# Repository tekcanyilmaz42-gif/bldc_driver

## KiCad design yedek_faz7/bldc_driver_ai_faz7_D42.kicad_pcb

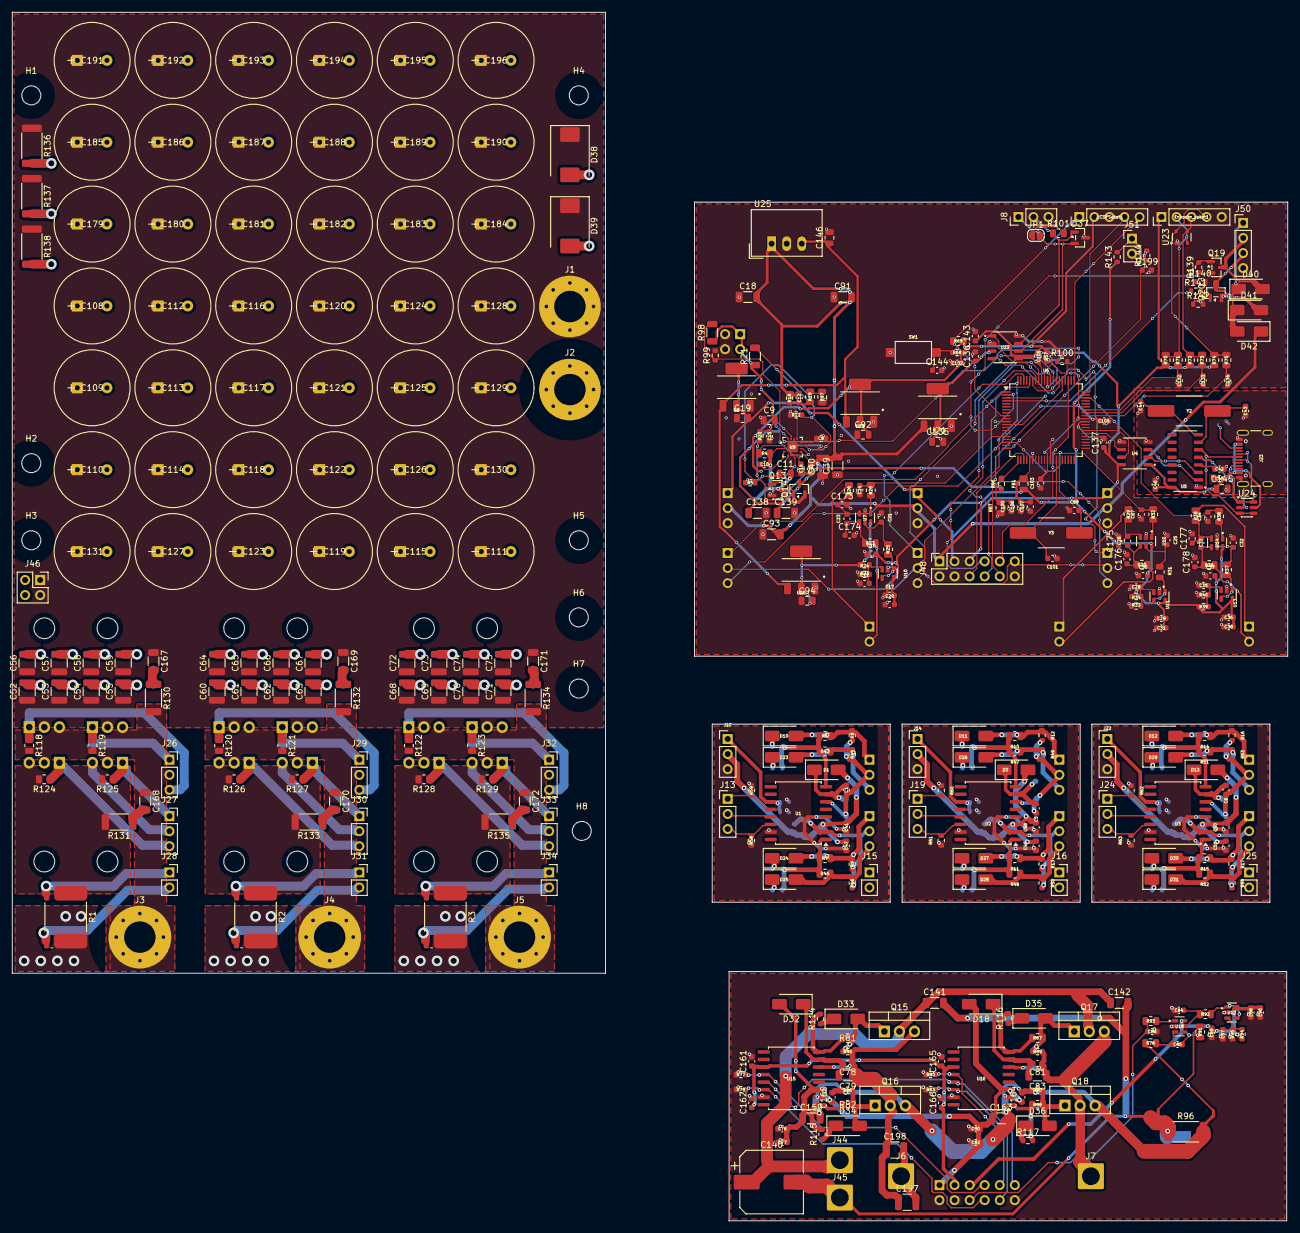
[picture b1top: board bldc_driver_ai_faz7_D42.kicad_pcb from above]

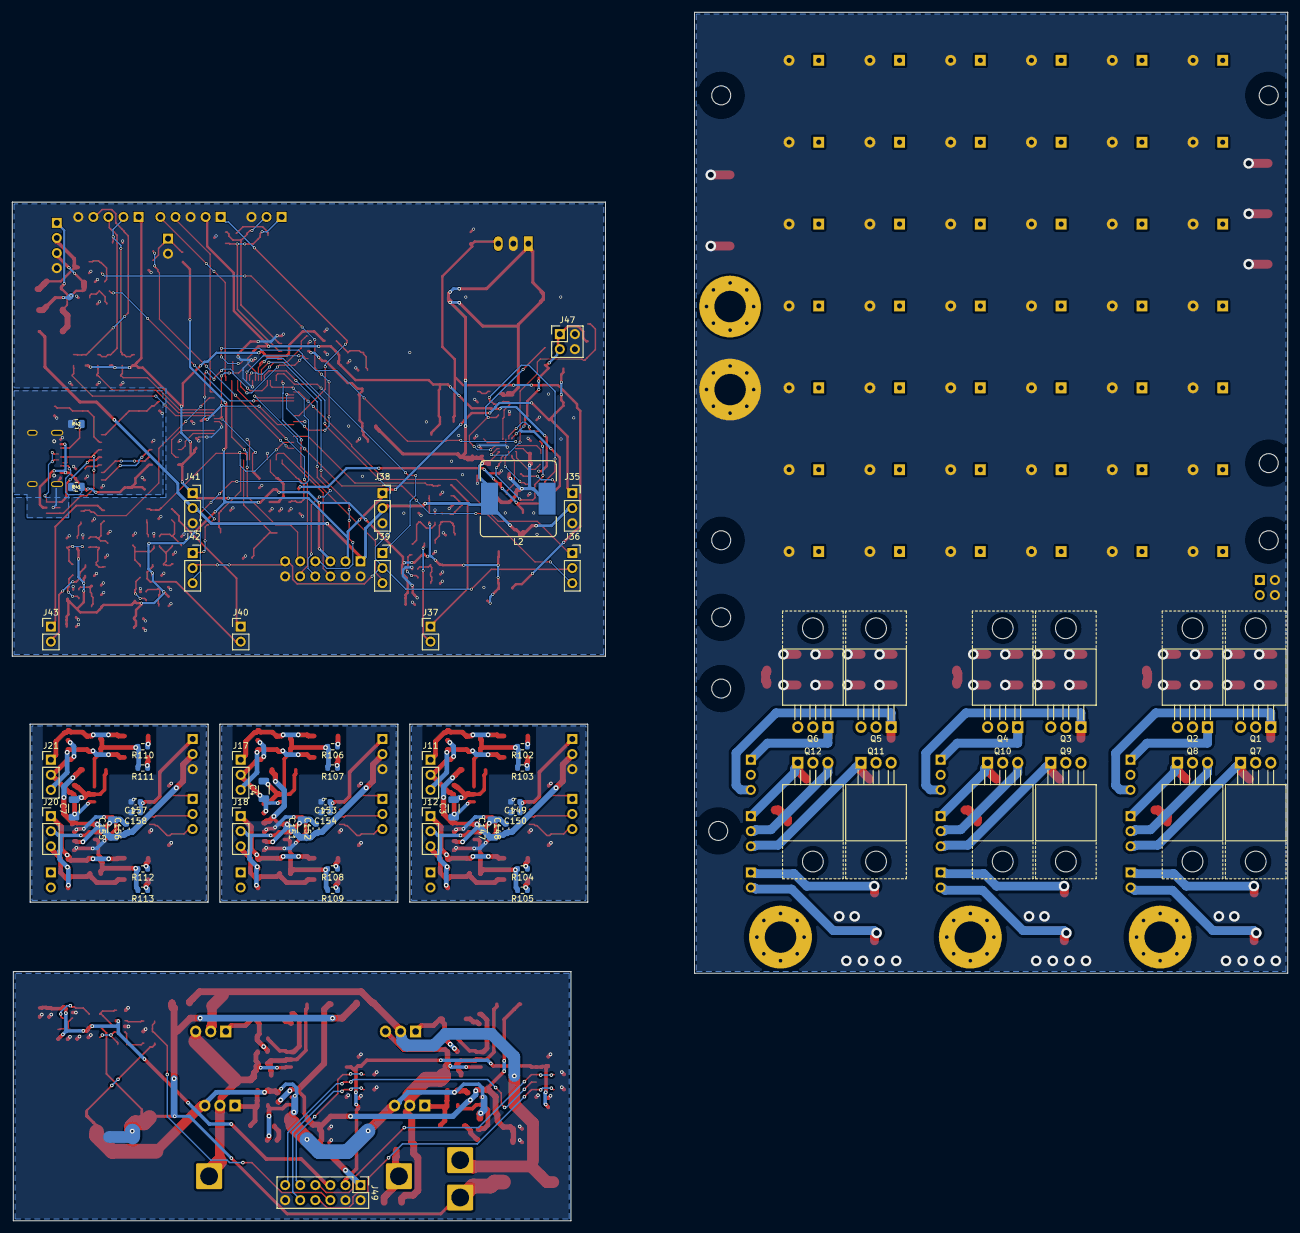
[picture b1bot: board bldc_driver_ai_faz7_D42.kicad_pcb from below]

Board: 2 copper layers, 215.0 x 203.7 mm, 473 parts (60 on the bottom side), 174 nets.

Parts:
C1, C5, C6, C10, C16, C17, C22, C28, C29, C30, C35, C36, C37, C42, C45, C46, C78, C81, C87, C88, C89, C100, C102, C103, C104, C105, C106, C136, C137, C143, C144, C148, C149, C152, C153, C156, C157, C160, C161, C164, C165, C199: 100nF; C_0603_1608Metric
C3, C4, C7, C79, C83: 2.2uF/25V; C_1206_3216Metric
C8: 10nF; C_0603_1608Metric
C9, C11: 100nF/100V; C_0805_2012Metric
C12: 4.7nF; C_0603_1608Metric
C13, C20, C31, C38, C41, C47, C48, C49, C50, C51, C76, C77, C80, C82, C90, C107, C150, C154, C158, C162, C166: 1uF; C_0603_1608Metric
C14, C15: 10uF; C_0603_1608Metric
C18, C39, C40, C91, C93: 10uF/25V; C_1206_3216Metric
C19, C92, C94, C146: 22uF/10V; C_0805_2012Metric
C21, C25, C32, C84: 1nF C0G; C_0603_1608Metric
C23, C26, C33: 220nF; C_0603_1608Metric
C24, C27, C34, C85, C86, C132, C133, C134, C173, C174, C175, C176, C177, C178: 1nF; C_0603_1608Metric
C43, C44, C99, C101: 27pF; C_0603_1608Metric
C52, C53, C54, C55, C56, C57, C58, C59, C60, C61, C62, C63, C64, C65, C66, C67, C68, C69, C70, C71, C72, C73, C74, C75, C197, C198: 4.7uF/100V; C_1210_3225Metric
C108, C109, C110, C111, C112, C113, C114, C115, C116, C117, C118, C119, C120, C121, C122, C123, C124, C125, C126, C127, C128, C129, C130, C131, C179, C180, C181, C182, C183, C184, C185, C186, C187, C188, C189, C190, C191, C192, C193, C194, C195, C196: 470uF/63V; KLH-063V471MH200-TA5.0
C135: 10uF/16V; C_0805_2012Metric
C138, C139, C141, C142: 2.2uF/100V; C_1206_3216Metric
C140: 220uF/63V; CP_Elec_10x10.5
C145: 4.7uF/10V; C_0805_2012Metric
C147, C151, C155, C159, C163: 22uF/25V; C_1206_3216Metric
C167, C168, C169, C170, C171, C172: 4.7nF/100V C0G; C_1206_3216Metric
D1, D2, D13, D18, D32: US1D; D_SMA
D10, D11, D12, D23, D24, D25, D26, D27, D28, D29, D30, D31, D33, D34, D35, D36, D40, D41: SS18; D_SMA
D37: NUP2105L; SOT-23
D38, D39: 5.0SMDJ58CA; D_SMC
D42: SS34; D_SMA
Enkoder_soket1: Conn_01x05_Socket; PinHeader_1x05_P2.54mm_Vertical
FB1: FerriteBead; C_0805_2012Metric
H1, H2, H3, H4, H5, H6, H7, H8: M3_Sogutucu; MountingHole_3.2mm_M3
J1: M5_Lug_VBAT; MountingHole_5.3mm_M5_Pad_Via
J2: M5_Lug_GND; MountingHole_5.3mm_M5_Pad_Via
J3: M5_Lug_U; MountingHole_5.3mm_M5_Pad_Via
J4: M5_Lug_V; MountingHole_5.3mm_M5_Pad_Via
J5: M5_Lug_W; MountingHole_5.3mm_M5_Pad_Via
J6, J7: Conn_01x01_Pin; SolderWire-2.5sqmm_1x01_D2.4mm_OD4.4mm
J8: CAN-bus; PinHeader_1x03_P2.54mm_Vertical
J10: Pwr_U; PinHeader_1x03_P2.54mm_Vertical
J11: Gate_H_U; PinHeader_1x03_P2.54mm_Vertical
J12: Gate_L_U; PinHeader_1x03_P2.54mm_Vertical
J13: Ctrl_U; PinHeader_1x03_P2.54mm_Vertical
J14: Pwr_V; PinHeader_1x03_P2.54mm_Vertical
J15: Sense_U_stack; PinSocket_1x02_P2.54mm_Vertical
J16: Sense_V_stack; PinSocket_1x02_P2.54mm_Vertical
J17: Gate_H_V; PinHeader_1x03_P2.54mm_Vertical
J18: Gate_L_V; PinHeader_1x03_P2.54mm_Vertical
J19: Ctrl_V; PinHeader_1x03_P2.54mm_Vertical
J20: Gate_L_W; PinHeader_1x03_P2.54mm_Vertical
J21: Gate_H_W; PinHeader_1x03_P2.54mm_Vertical
J22: Pwr_W; PinHeader_1x03_P2.54mm_Vertical
J23: USB_IN; USB_C_Receptacle_GCT_USB4105-xx-A_16P_TopMnt_Horizontal
J24: Ctrl_W; PinHeader_1x03_P2.54mm_Vertical
J25: Sense_W_stack; PinSocket_1x02_P2.54mm_Vertical
J26: Gate_H_U; PinSocket_1x03_P2.54mm_Vertical
J27: Gate_L_U; PinSocket_1x03_P2.54mm_Vertical
J28: Sense_U; PinSocket_1x02_P2.54mm_Vertical
J29: Gate_H_V; PinSocket_1x03_P2.54mm_Vertical
J30: Gate_L_V; PinSocket_1x03_P2.54mm_Vertical
J31: Sense_V; PinSocket_1x02_P2.54mm_Vertical
J32: Gate_H_W; PinSocket_1x03_P2.54mm_Vertical
J33: Gate_L_W; PinSocket_1x03_P2.54mm_Vertical
J34: Sense_W; PinSocket_1x02_P2.54mm_Vertical
J35: Pwr_U; PinSocket_1x03_P2.54mm_Vertical
J36: Ctrl_U; PinSocket_1x03_P2.54mm_Vertical
J37: Sense_U; PinHeader_1x02_P2.54mm_Vertical
J38: Pwr_V; PinSocket_1x03_P2.54mm_Vertical
J39: Ctrl_V; PinSocket_1x03_P2.54mm_Vertical
J40: Sense_V; PinHeader_1x02_P2.54mm_Vertical
J41: Pwr_W; PinSocket_1x03_P2.54mm_Vertical
J42: Ctrl_W; PinSocket_1x03_P2.54mm_Vertical
J43: Sense_W; PinHeader_1x02_P2.54mm_Vertical
J44: VBAT_EESM; SolderWire-2.5sqmm_1x01_D2.4mm_OD4.4mm
J45: GND_EESM; SolderWire-2.5sqmm_1x01_D2.4mm_OD4.4mm
J46: Riser_VBAT_GND; PinSocket_2x02_P2.54mm_Vertical
J47: Riser_VBAT_GND; PinHeader_2x02_P2.54mm_Vertical
J48: EESM_Bus; PinSocket_2x06_P2.54mm_Vertical
J49: EESM_Bus; PinHeader_2x06_P2.54mm_Vertical
J50: Kontaktor; PinHeader_1x04_P2.54mm_Vertical
J51: NTC_sogutucu; PinHeader_1x02_P2.54mm_Vertical
JICSPSoket1: Conn_01x05_Pin; PinHeader_1x05_P2.54mm_Vertical
JP1: CAN 120R; SolderJumper-2_P1.3mm_Open_RoundedPad1.0x1.5mm
L2: 33uH Isat>=3A; L_Bourns_SRR1260
NT7, NT8: NetTie; NetTie-2_SMD_Pad0.5mm
NT9: NetTie; NetTie-2_SMD_Pad2.0mm
Q1, Q2, Q3, Q4, Q5, Q6, Q7, Q8, Q9, Q10, Q11, Q12: IRFB4110PBF; TO-220-3_Horizontal_TabUp
Q13, Q14: IRLML0100TRPBF; SOT-23
Q15, Q16, Q17, Q18: IRFB4110PBF; TO-220-3_Vertical
Q19, Q20: AO3400A; SOT-23
R1, R2, R3: 0.2mR 4-terminal; R_Shunt_Isabellenhuette_BVR4026
R4: 5.6k; R_0805_2012Metric
R5, R100: 100k; R_0603_1608Metric
R6, R7, R10, R11, R14, R15, R25, R26, R27, R29, R30, R31, R35, R36, R37, R43, R45, R47, R48, R51, R52, R76, R81, R82, R87, R88, R91, R92: 10; R_0805_2012Metric
R8, R9, R12, R13, R16, R17, R23, R24, R33, R34, R39, R40, R44, R46, R49, R50, R53, R54, R58, R59, R60, R61, R62, R63, R68, R77, R78, R80, R83, R85, R86, R89, R90, R94, R95, R140, R142: 10k; R_0603_1608Metric
R18: 20k; R_0603_1608Metric
R19: 1.05k 1%; R_0805_2012Metric
R20, R102, R103, R104, R105, R106, R107, R108, R109, R110, R111, R112, R113, R114, R115, R116, R117: 2.2; R_0603_1608Metric
R21: 100k; R_1206_3216Metric
R22: 60k; R_0603_1608Metric_Pad0.98x0.95mm_HandSolder
R28, R32, R38, R69, R71, R73, R75, R93: 100; R_0805_2012Metric
R41, R42: 5.1k; R_0805_2012Metric
R57: 2.2k; R_0603_1608Metric
R66: 100k; R_0603_1608Metric_Pad0.98x0.95mm_HandSolder
R67: 4.7k; R_0805_2012Metric
R70, R72, R74: 1.5k; R_0805_2012Metric
R96: 5mR 2512 3W; R_2512_6332Metric
R97: 0R; R_0805_2012Metric
R98: 470k; R_1206_3216Metric
R99: 27k; R_0603_1608Metric
R101: 120; R_0805_2012Metric
R118, R119, R120, R121, R122, R123, R124, R125, R126, R127, R128, R129: 10k; R_0805_2012Metric
R130, R131, R132, R133, R134, R135: 2.2; R_2010_5025Metric
R136, R137, R138: 10k 1W; R_2512_6332Metric
R139, R141: 100; R_0603_1608Metric
R143: 10k 0.1%; R_0603_1608Metric
R144: 1k; R_0603_1608Metric
SW1: SW_Push; SW_SPST_CK_RS282G05A3
U1, U2, U3, U15, U16: IR2110S; SOIC-16W_7.5x10.3mm_P1.27mm
U4: ADuM1201
U5: CH340G
U6: dsPIC33CK256MP508; LQFP-80_12x12mm_P0.5mm
U7, U12, U14, U18: INA181
U8, U19, U20: LDL1117S33R; NCP1117
U9: MIC2128
U10, U11, U13, U17: TLV9001
U21: LDL1117S50R; NCP1117
U22: TJA1051
U23: SP0503BAHT; SOT-143
U24: USBLC6-2SC6; SOT-23-6
U25: TSR 1-2450; Converter_DCDC_TRACO_TSR-1_THT
Y2, Y3: 12MHz Kristal; AS-12.000-18-3030-EXT-SMD-TR

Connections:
3V3_ANA: C16.2, C17.2, C20.2, C29.2, C30.2, C31.2, C36.2, C37.2, C38.2, C88.2, C89.2, C90.2, C94.2, FB1.1, J48.5, J49.5, R23.2, R33.2, R39.2, R94.2, R143.1, U7.6 (VS), U10.5 (V+), U11.5 (V+), U12.6 (VS), U13.5 (V+), U14.6 (VS), U17.5 (V+), U18.6 (VS), U20.2 (VO), U20.4 (TAB)
3V3_IO: C19.2, C137.1, C143.1, C149.1, C150.1, C153.1, C154.1, C157.1, C158.1, C161.1, C162.1, C165.1, C166.1, Enkoder_soket1.1, J10.1, J14.1, J22.1, J35.1, J38.1, J41.1, J48.3, J49.3, R57.1, R70.1, R72.1, R74.1, U1.11 (VDD), U2.11 (VDD), U3.11 (VDD), U4.8 (VDD2), U8.2 (VO), U8.4 (TAB), U15.11 (VDD), U16.11 (VDD), U22.5 (VIO)
3V3_MCU: C92.2, C102.2, C103.2, C104.2, C105.2, JICSPSoket1.2, R68.2, R100.2, U6.12 (VDD), U6.31 (VDD), U6.51 (VDD), U6.71 (VDD), U19.2 (VO), U19.4 (TAB)
5V_CAN: C135.1, C136.1, U21.2, U21.4, U22.3 (VCC)
5V_USB: C45.2, C46.2, C145.1, J23.A4 (VBUS), J23.A9 (VBUS), J23.B4 (VBUS), J23.B9 (VBUS), U4.1 (VDD1), U5.16 (VCC), U24.5
12V: C12.2, C13.2, C18.2, C39.2, C40.2, C41.2, C47.2, C48.2, C49.2, C50.2, C51.2, C76.2, C77.2, C80.2, C82.2, C91.2, C93.2, C147.1, C148.1, C151.1, C152.1, C155.1, C156.1, C159.1, C160.1, C163.1, C164.1, D1.2 (A), D2.2 (A), D13.2 (A), D18.2, D32.2, D42.1, J10.2, J14.2, J22.2, J35.2, J38.2, J41.2, J48.1, J49.1, L2.2, R18.2, U1.3 (VCC), U2.3 (VCC), U3.3 (VCC), U9.9 (EXTVDD), U15.3 (VCC), U16.3 (VCC), U21.3, U25.1
/Katman1_Guc_Karti/SNB_UH: C167.2, R130.1
/Katman1_Guc_Karti/SNB_UL: C168.2, R131.1
/Katman1_Guc_Karti/SNB_VH: C169.2, R132.1
/Katman1_Guc_Karti/SNB_VL: C170.2, R133.1
/Katman1_Guc_Karti/SNB_WH: C171.2, R134.1
/Katman1_Guc_Karti/SNB_WL: C172.2, R135.1
/Katman2_GateDriver_U/HO_U: R6.1, R43.1, R102.2, R103.2, U1.8 (HO)
/Katman2_GateDriver_U/HO_U_OFF_D10: D10.1 (K), R102.1
/Katman2_GateDriver_U/HO_U_OFF_D23: D23.1 (K), R103.1
/Katman2_GateDriver_U/LO_U: R7.1, R45.1, R104.2, R105.2, U1.1 (LO)
/Katman2_GateDriver_U/LO_U_OFF_D24: D24.1 (K), R104.1
/Katman2_GateDriver_U/LO_U_OFF_D25: D25.1 (K), R105.1
/Katman2_GateDriver_U/VB_U: C1.2, C3.2, D1.1 (K), U1.7 (VB)
/Katman2_GateDriver_V/HO_V: R10.1, R47.1, R106.2, R107.2, U2.8 (HO)
/Katman2_GateDriver_V/HO_V_OFF_D11: D11.1 (K), R106.1
/Katman2_GateDriver_V/HO_V_OFF_D26: D26.1 (K), R107.1
/Katman2_GateDriver_V/LO_V: R11.1, R48.1, R108.2, R109.2, U2.1 (LO)
/Katman2_GateDriver_V/LO_V_OFF_D27: D27.1 (K), R108.1
/Katman2_GateDriver_V/LO_V_OFF_D28: D28.1 (K), R109.1
/Katman2_GateDriver_V/VB_V: C4.2, C5.2, D2.1 (K), U2.7 (VB)
/Katman2_GateDriver_W/HO_W: R14.1, R51.1, R110.2, R111.2, U3.8 (HO)
/Katman2_GateDriver_W/HO_W_OFF_D12: D12.1 (K), R110.1
/Katman2_GateDriver_W/HO_W_OFF_D29: D29.1 (K), R111.1
/Katman2_GateDriver_W/LO_W: R15.1, R52.1, R112.2, R113.2, U3.1 (LO)
/Katman2_GateDriver_W/LO_W_OFF_D30: D30.1 (K), R112.1
/Katman2_GateDriver_W/LO_W_OFF_D31: D31.1 (K), R113.1
/Katman2_GateDriver_W/VB_W: C6.2, C7.2, D13.1 (K), U3.7 (VB)
/Katman3_Kontrol_Karti/5V_SYS: C146.1, U8.3 (VI), U19.3 (VI), U20.3 (VI), U25.3
/Katman3_Kontrol_Karti/BUCK_BST: C10.2, U9.4 (BST)
/Katman3_Kontrol_Karti/BUCK_EN: R98.2, R99.1, U9.10 (EN)
/Katman3_Kontrol_Karti/BUCK_FB_DIV: R19.1, R97.2
/Katman3_Kontrol_Karti/BUCK_FREQ: R21.2, R22.2, U9.11 (FREQ)
/Katman3_Kontrol_Karti/BUCK_ILIM: R4.1, U9.2 (ILIM)
/Katman3_Kontrol_Karti/BUCK_PG: R100.1, U6.66 (RC10/RP58), U9.1 (PG)
/Katman3_Kontrol_Karti/BUCK_PVDD: C14.2, R20.1, U9.8 (PVDD)
/Katman3_Kontrol_Karti/BUCK_RIPPLE: C11.1, R5.2
/Katman3_Kontrol_Karti/BUCK_SS: C8.2, U9.12 (SS)
/Katman3_Kontrol_Karti/BUCK_SW: C10.1, C11.2, L2.1, Q13.3, Q14.2, R4.2, U9.3 (SW)
/Katman3_Kontrol_Karti/BUCK_VDD: C15.2, R20.2, U9.15 (VDD)
/Katman3_Kontrol_Karti/CANH: D37.1, J8.2, R101.1, U22.7 (CANH)
/Katman3_Kontrol_Karti/CANL: D37.2, J8.1, JP1.2, U22.6 (CANL)
/Katman3_Kontrol_Karti/CAN_TERM: JP1.1, R101.2
/Katman3_Kontrol_Karti/CH340_V3: C42.2, U5.4 (V3)
/Katman3_Kontrol_Karti/CH340_XI: C43.2, U5.7 (XI), Y2.1
/Katman3_Kontrol_Karti/CH340_XO: C44.2, U5.8 (XO), Y2.2
/Katman3_Kontrol_Karti/CH_RXD: U4.2 (VIA), U5.3 (RXD)
/Katman3_Kontrol_Karti/CH_TXD: U4.3 (VIB), U5.2 (TXD)
/Katman3_Kontrol_Karti/COIL_12V: D40.1, D41.1, D42.2, J50.1
/Katman3_Kontrol_Karti/CONT_EN: R139.1, U6.2 (RE0)
/Katman3_Kontrol_Karti/CONT_EN_G: Q19.1, R139.2, R140.1
/Katman3_Kontrol_Karti/CONT_K: D40.2, J50.2, Q19.3
/Katman3_Kontrol_Karti/DH: Q14.1, U9.5 (DH)
/Katman3_Kontrol_Karti/DL: Q13.1, U9.7 (DL)
/Katman3_Kontrol_Karti/Enkoder_A: C132.2, R71.2, U6.54 (RD5/RP69)
/Katman3_Kontrol_Karti/Enkoder_A_soket: Enkoder_soket1.2, R70.2, R71.1, U23.2
/Katman3_Kontrol_Karti/Enkoder_B: C133.2, R73.2, U6.53 (RD6/RP70)
/Katman3_Kontrol_Karti/Enkoder_B_soket: Enkoder_soket1.3, R72.2, R73.1, U23.3
/Katman3_Kontrol_Karti/Enkoder_Z: C134.2, R75.2, U6.52 (RD7/RP71)
/Katman3_Kontrol_Karti/Enkoder_Z_soket: Enkoder_soket1.4, R74.2, R75.1, U23.4
/Katman3_Kontrol_Karti/FB: C12.1, R5.1, R18.1, R19.2, U9.13 (FB)
/Katman3_Kontrol_Karti/IN181_Uout: C24.2, R28.1, U6.16 (RA0)
/Katman3_Kontrol_Karti/IN181_Vout: C27.2, R32.1, U6.18 (RA1), U6.33 (RC3/RP51)
/Katman3_Kontrol_Karti/IN181_Wout: C34.2, R38.1, U6.58 (RB7/RP39)
/Katman3_Kontrol_Karti/MCLR: JICSPSoket1.1, R69.1, U6.9 (MCLR)
/Katman3_Kontrol_Karti/MCLR_SW: C144.1, R68.1, R69.2, SW1.2
/Katman3_Kontrol_Karti/NTC_ADC: C199.1, R144.2, U6.20 (RA2)
/Katman3_Kontrol_Karti/NTC_HS: J51.1, R143.2, R144.1
/Katman3_Kontrol_Karti/OSCI_DSP: C101.2, U6.34 (OSCI/CLKI), Y3.2
/Katman3_Kontrol_Karti/OSCO_DSP: C99.2, U6.35 (OSCO/CLKO), Y3.1
/Katman3_Kontrol_Karti/PGC1: JICSPSoket1.5, U6.61 (RB9/RP41)
/Katman3_Kontrol_Karti/PGD1: JICSPSoket1.4, U6.60 (RB8/RP40)
/Katman3_Kontrol_Karti/PRE_EN: R141.1, U6.4 (RE1)
/Katman3_Kontrol_Karti/PRE_EN_G: Q20.1, R141.2, R142.1
/Katman3_Kontrol_Karti/PRE_K: D41.2, J50.3, Q20.3
/Katman3_Kontrol_Karti/RXD_DSP: U4.6 (VOB), U6.46 (RC8/RP56)
/Katman3_Kontrol_Karti/RXD_DSP_can: U6.68 (RD4/RP68), U22.4 (RXD)
/Katman3_Kontrol_Karti/TLV_IN+_u: C22.2, R23.1, R24.2, U10.3 (IN+)
/Katman3_Kontrol_Karti/TLV_IN+_v: C28.2, R33.1, R34.2, U11.3 (IN+)
/Katman3_Kontrol_Karti/TLV_IN+_w: C35.2, R39.1, R40.2, U13.3 (IN+)
/Katman3_Kontrol_Karti/TXD_DSP: U4.7 (VOA), U6.47 (RC9/RP57)
/Katman3_Kontrol_Karti/TXD_DSP_can: U6.69 (RD3/RP67), U22.1 (TXD)
/Katman3_Kontrol_Karti/USB_CC1: J23.A5 (CC1), R41.2
/Katman3_Kontrol_Karti/USB_CC2: J23.B5 (CC2), R42.2
/Katman3_Kontrol_Karti/USB_DM: J23.A7 (D-), J23.B7 (D-), U5.6 (UD-), U24.3, U24.4
/Katman3_Kontrol_Karti/USB_DP: J23.A6 (D+), J23.B6 (D+), U5.5 (UD+), U24.1, U24.6
/Katman3_Kontrol_Karti/U_AMP_OUT: R28.2, U7.1 (OUT)
/Katman3_Kontrol_Karti/U_INN_F: C23.1, C174.1, R27.1, U7.4 (IN-)
/Katman3_Kontrol_Karti/U_INP_F: C23.2, C173.1, R26.1, U7.3 (IN+)
/Katman3_Kontrol_Karti/U_VREF: C21.2, R25.1, U7.5 (REF)
/Katman3_Kontrol_Karti/U_VREF_BUF: R25.2, U10.1 (OUT), U10.4 (IN-)
/Katman3_Kontrol_Karti/V_AMP_OUT: R32.2, U12.1 (OUT)
/Katman3_Kontrol_Karti/V_BUS_SENSE: C100.2, R66.2, R67.2, U6.21 (RA3)
/Katman3_Kontrol_Karti/V_INN_F: C26.1, C176.1, R30.1, U12.4 (IN-)
/Katman3_Kontrol_Karti/V_INP_F: C26.2, C175.1, R29.1, U12.3 (IN+)
/Katman3_Kontrol_Karti/V_VREF: C25.2, R31.1, U12.5 (REF)
/Katman3_Kontrol_Karti/V_VREF_BUF: R31.2, U11.1 (OUT), U11.4 (IN-)
/Katman3_Kontrol_Karti/W_AMP_OUT: R38.2, U14.1 (OUT)
/Katman3_Kontrol_Karti/W_INN_F: C33.1, C178.1, R36.1, U14.4 (IN-)
/Katman3_Kontrol_Karti/W_INP_F: C33.2, C177.1, R35.1, U14.3 (IN+)
/Katman3_Kontrol_Karti/W_VREF: C32.2, R37.1, U14.5 (REF)
/Katman3_Kontrol_Karti/W_VREF_BUF: R37.2, U13.1 (OUT), U13.4 (IN-)
/Katman4_EESM_Modulu/G_P1H: D33.2, Q15.1, R81.2, R85.2
/Katman4_EESM_Modulu/G_P1L: D34.2, Q16.1, R82.2, R86.2
/Katman4_EESM_Modulu/G_P2H: D35.2, Q17.1, R87.2, R89.2
/Katman4_EESM_Modulu/G_P2L: D36.2, Q18.1, R88.2, R90.2
/Katman4_EESM_Modulu/HO_P1: R81.1, R114.2, U15.8 (HO)
/Katman4_EESM_Modulu/HO_P1_OFF_D33: D33.1, R114.1
/Katman4_EESM_Modulu/HO_P2: R87.1, R116.2, U16.8 (HO)
/Katman4_EESM_Modulu/HO_P2_OFF_D35: D35.1, R116.1
/Katman4_EESM_Modulu/IF_AMP_OUT: R93.2, U18.1 (OUT)
/Katman4_EESM_Modulu/IF_H: C159.2, C160.2, C163.2, C164.2, NT7.1, Q16.3, Q18.3, R86.1, R90.1, R96.2, U15.2 (COM), U16.2 (COM)
/Katman4_EESM_Modulu/IF_INN_F: C85.1, R91.1, U18.4 (IN-)
/Katman4_EESM_Modulu/IF_INP_F: C85.2, R76.1, U18.3 (IN+)
/Katman4_EESM_Modulu/IF_SNS_N: NT8.2, R91.2
/Katman4_EESM_Modulu/IF_SNS_P: NT7.2, R76.2
/Katman4_EESM_Modulu/IF_VREF: C84.2, R92.1, U18.5 (REF)
/Katman4_EESM_Modulu/IF_VREF_BUF: R92.2, U17.1 (OUT), U17.4 (IN-)
/Katman4_EESM_Modulu/LO_P1: R82.1, R115.2, U15.1 (LO)
/Katman4_EESM_Modulu/LO_P1_OFF_D34: D34.1, R115.1
/Katman4_EESM_Modulu/LO_P2: R88.1, R117.2, U16.1 (LO)
/Katman4_EESM_Modulu/LO_P2_OFF_D36: D36.1, R117.1
/Katman4_EESM_Modulu/PGND_EESM: C140.2, C141.2, C142.2, J45.1, NT8.1, NT9.1, R96.1
/Katman4_EESM_Modulu/PRIMER_1_TR: C197.2, C198.2, J6.1
/Katman4_EESM_Modulu/TLV_IN+_IF: C87.2, R94.1, R95.2, U17.3 (IN+)
/Katman4_EESM_Modulu/VB_P1: C78.2, C79.2, D32.1, U15.7 (VB)
/Katman4_EESM_Modulu/VB_P2: C81.2, C83.2, D18.1, U16.7 (VB)
/Katman4_EESM_Modulu/primer_1: C78.1, C79.1, C197.1, C198.1, Q15.3, Q16.2, R85.1, U15.6 (VS)
/Katman4_EESM_Modulu/primer_2: C81.1, C83.1, J7.1, Q17.3, Q18.2, R89.1, U16.6 (VS)
AVDD: C106.2, C107.2, FB1.2, U6.25 (AVDD)
GND: C8.1, C9.1, C13.1, C14.1, C15.1, C16.1, C17.1, C18.1, C19.1, C20.1, C21.1, C22.1, C24.1, C25.1, C27.1, C28.1, C29.1, C30.1, C31.1, C32.1, C34.1, C35.1, C36.1, C37.1, C38.1, C39.1, C40.1, C41.1, C47.1, C48.1, C49.1, C50.1, C51.1, C52.2, C53.2, C54.2, C55.2, C56.2, C57.2, C58.2, C59.2, C60.2, C61.2, C62.2, C63.2, C64.2, C65.2, C66.2, C67.2, C68.2, C69.2, C70.2, C71.2, C72.2, C73.2, C74.2, C75.2, C76.1, C77.1, C80.1, C82.1, C84.1, C86.1, C87.1, C88.1, C89.1, C90.1, C91.1, C92.1, C93.1, C94.1, C99.1, C100.1, C101.1, C102.1, C103.1, C104.1, C105.1, C106.1, C107.1, C108.2 (-), C109.2 (-), C110.2 (-), C111.2 (-), C112.2 (-), C113.2 (-), C114.2 (-), C115.2 (-), C116.2 (-), C117.2 (-), C118.2 (-), C119.2 (-), C120.2 (-), C121.2 (-), C122.2 (-), C123.2 (-), C124.2 (-), C125.2 (-), C126.2 (-), C127.2 (-), C128.2 (-), C129.2 (-), C130.2 (-), C131.2 (-), C132.1, C133.1, C134.1, C135.2, C136.2, C137.2, C138.2, C139.2, C143.2, C144.2, C146.2, C149.2, C150.2, C153.2, C154.2, C157.2, C158.2, C161.2, C162.2, C165.2, C166.2, C173.2, C174.2, C175.2, C176.2, C177.2, C178.2, C179.2 (-), C180.2 (-), C181.2 (-), C182.2 (-), C183.2 (-), C184.2 (-), C185.2 (-), C186.2 (-), C187.2 (-), C188.2 (-), C189.2 (-), C190.2 (-), C191.2 (-), C192.2 (-), C193.2 (-), C194.2 (-), C195.2 (-), C196.2 (-), C199.2, D37.3, D38.2, D39.2, Enkoder_soket1.5, J2.1, J8.3, J10.3, J14.3, J22.3, J35.3, J38.3, J41.3, J46.2, J46.4, J47.2, J47.4, J48.2, J48.4, J48.12, J49.2, J49.4, J49.12, J50.4, J51.2, JICSPSoket1.3, NT9.2, Q13.2, Q19.2, Q20.2, R1.4, R2.4, R3.4, R22.1, R24.1, R34.1, R40.1, R58.1, R59.2, R60.2, R61.1, R62.2, R63.1, R67.1, R77.2, R78.1, R80.2, R83.1, R95.1, R97.1, R99.2, R136.2, R137.2, R138.2, R140.2, R142.2, SW1.1, U1.15 (VSS), U2.15 (VSS), U3.15 (VSS), U4.5 (GND2), U6.11 (VSS), U6.26 (AVSS), U6.32 (VSS), U6.50 (VSS), U6.70 (VSS), U7.2 (GND), U8.1 (GND/ADJ), U9.6 (PGND), U9.14 (AGND), U9.17 (EP), U10.2 (V-), U11.2 (V-), U12.2 (GND), U13.2 (V-), U14.2 (GND), U15.15 (VSS), U16.15 (VSS), U17.2 (V-), U18.2 (GND), U19.1 (GND/ADJ), U20.1 (GND/ADJ), U21.1, U22.2 (GND), U22.8 (S), U23.1, U25.2
GND_PC: C42.1, C43.1, C44.1, C45.1, C46.1, C145.2, J23.A1 (GND), J23.A12 (GND), J23.B1 (GND), J23.B12 (GND), J23.SH, R41.1, R42.1, U4.4 (GND1), U5.1 (GND), U24.2
G_UH1: D10.2 (A), J11.1, J26.1, Q2.1, R6.2, R8.2, R119.1
G_UH2: D23.2 (A), J11.3, J26.3, Q1.1, R43.2, R44.2, R118.1
G_UH_IN: J13.1, J36.1, R59.1, U1.12 (HIN), U6.1 (RB14/RP46)
G_UL1: D24.2 (A), J12.1, J27.1, Q8.1, R7.2, R9.2, R125.1
G_UL2: D25.2 (A), J12.3, J27.3, Q7.1, R45.2, R46.2, R124.1
G_UL_IN: J13.3, J36.3, R58.2, U1.14 (LIN), U6.3 (RB15/RP47)
G_VH1: D11.2 (A), J17.1, J29.1, Q4.1, R10.2, R12.2, R121.1
G_VH2: D26.2 (A), J17.3, J29.3, Q3.1, R47.2, R49.2, R120.1
G_VH_IN: J19.1, J39.1, R60.1, U2.12 (HIN), U6.78 (RB12/RP44)
G_VL1: D27.2 (A), J18.1, J30.1, Q10.1, R11.2, R13.2, R127.1
G_VL2: D28.2 (A), J18.3, J30.3, Q9.1, R48.2, R50.2, R126.1
G_VL_IN: J19.3, J39.3, R61.2, U2.14 (LIN), U6.80 (RB13/RP45)
G_WH1: D12.2 (A), J21.1, J32.1, Q6.1, R14.2, R16.2, R123.1
G_WH2: D29.2 (A), J21.3, J32.3, Q5.1, R51.2, R53.2, R122.1
G_WH_IN: J24.1, J42.1, R62.1, U3.12 (HIN), U6.75 (RB10/RP42)
G_WL1: D30.2 (A), J20.1, J33.1, Q12.1, R15.2, R17.2, R129.1
G_WL2: D31.2 (A), J20.3, J33.3, Q11.1, R52.2, R54.2, R128.1
G_WL_IN: J24.3, J42.3, R63.2, U3.14 (LIN), U6.76 (RB11/RP43)
IN181_IFout: C86.2, J48.6, J49.6, R93.1, U6.23 (RA4)
Phase_U: C1.1, C3.1, C168.1, J3.1, J11.2, J26.2, Q1.3, Q2.3, Q7.2, Q8.2, R8.1, R44.1, R118.2, R119.2, R130.2, U1.6 (VS)
Phase_V: C4.1, C5.1, C170.1, J4.1, J17.2, J29.2, Q3.3, Q4.3, Q9.2, Q10.2, R12.1, R49.1, R120.2, R121.2, R132.2, U2.6 (VS)
Phase_W: C6.1, C7.1, C172.1, J5.1, J21.2, J32.2, Q5.3, Q6.3, Q11.2, Q12.2, R16.1, R53.1, R122.2, R123.2, R134.2, U3.6 (VS)
SD: J13.2, J19.2, J24.2, J36.2, J39.2, J42.2, J48.11, J49.11, R57.2, U1.13 (SD), U2.13 (SD), U3.13 (SD), U6.72 (RD2/RP66), U15.13 (SD), U16.13 (SD)
USH: C147.2, C148.2, J12.2, J27.2, Q7.3, Q8.3, R1.1, R9.1, R46.1, R124.2, R125.2, R131.2, U1.2 (COM)
U_SNS_N: J15.2, J28.2, J37.2, R1.3, R27.2
U_SNS_P: J15.1, J28.1, J37.1, R1.2, R26.2
VBAT: C9.2, C52.1, C53.1, C54.1, C55.1, C56.1, C57.1, C58.1, C59.1, C60.1, C61.1, C62.1, C63.1, C64.1, C65.1, C66.1, C67.1, C68.1, C69.1, C70.1, C71.1, C72.1, C73.1, C74.1, C75.1, C108.1 (+), C109.1 (+), C110.1 (+), C111.1 (+), C112.1 (+), C113.1 (+), C114.1 (+), C115.1 (+), C116.1 (+), C117.1 (+), C118.1 (+), C119.1 (+), C120.1 (+), C121.1 (+), C122.1 (+), C123.1 (+), C124.1 (+), C125.1 (+), C126.1 (+), C127.1 (+), C128.1 (+), C129.1 (+), C130.1 (+), C131.1 (+), C138.1, C139.1, C140.1, C141.1, C142.1, C167.1, C169.1, C171.1, C179.1 (+), C180.1 (+), C181.1 (+), C182.1 (+), C183.1 (+), C184.1 (+), C185.1 (+), C186.1 (+), C187.1 (+), C188.1 (+), C189.1 (+), C190.1 (+), C191.1 (+), C192.1 (+), C193.1 (+), C194.1 (+), C195.1 (+), C196.1 (+), D38.1, D39.1, J1.1, J44.1, J46.1, J46.3, J47.1, J47.3, Q1.2, Q2.2, Q3.2, Q4.2, Q5.2, Q6.2, Q14.3, Q15.2, Q17.2, R21.1, R66.1, R98.1, R136.1, R137.1, R138.1, U9.16 (VIN)
VSH: C151.2, C152.2, J18.2, J30.2, Q9.3, Q10.3, R2.1, R13.1, R50.1, R126.2, R127.2, R133.2, U2.2 (COM)
V_SNS_N: J16.2, J31.2, J40.2, R2.3, R30.2
V_SNS_P: J16.1, J31.1, J40.1, R2.2, R29.2
WSH: C155.2, C156.2, J20.2, J33.2, Q11.3, Q12.3, R3.1, R17.1, R54.1, R128.2, R129.2, R135.2, U3.2 (COM)
W_SNS_N: J25.2, J34.2, J43.2, R3.3, R36.2
W_SNS_P: J25.1, J34.1, J43.1, R3.2, R35.2
primer_1_H: J48.7, J49.7, R77.1, U6.73 (RD1/RP65), U15.12 (HIN)
primer_1_L: J48.8, J49.8, R78.2, U6.74 (RD0/RP64), U15.14 (LIN)
primer_2_H: J48.9, J49.9, R80.1, U6.63 (RC4/RP52), U16.12 (HIN)
primer_2_L: J48.10, J49.10, R83.2, U6.65 (RC5/RP53), U16.14 (LIN)
